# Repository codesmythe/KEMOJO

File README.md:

# KEMOJO (Keyboard / Mouse / Joystick)

This board provides PS/2 keyboard, PS/2 mouse and Atari or MSX (single
button only) joystick support for an RCBus system. It uses the 40-pin
RCBus interface. 

The keyboard, mouse and joystick inputs are read by an ATmega 328P
microcontoller. (This is the same MCU that is in the Arduino UNO.) The
ATmega implements the [Atari ST IKBD
protcol](https://archive.org/details/Intelligent_Keyboard_ikbd_Protocol_Feb_26_1985/)
and communicates that protocol serially to an RCBus system via a
16C550 UART.

## Table of Contents
* [Hardware Documentation](#hardware-documentation)
  * [Schematic](#schematic)
  * [Connectors](#connectors)
  * [Jumpers](#jumpers)
  * [Bill of Materials](#bill-of-materials)
* [Firmware Documentation](#firmware-documentation)
* [Acknowledgements](#acknowledgements)

## Hardware Documentation

### Schematic

The board was created using [Kicad](https://www.kicad.org) version 8.0.

Click the image to download a PDF version of the schematic.

### Connectors

| Reference | Description                                                  |
| --------- | ------------------------------------------------------------ |
| J1        | In-system Programming (ISP) port for programming the ATmega328P firmware. |
| J2        | Atari or MSX Joystick 0, Male DE9 D-Sub. See J7 jumper settings below. |
| J3        | Atari or MSX Joystick 1, Male DE9 D-Sub. See J8 jumper settings below. |
| J4        | PS/2 6-pin Mini DIN connector for PS/2 keyboard.             |
| J5        | PS/2 6-pin Mini DIN connector for PS/2 mouse.                |
| J6        | [FTDI Friend](https://www.adafruit.com/product/284) connection to 16C550 UART. For debug purposes or UART-only operation. |

### Jumpers

| Reference | Description                             | Comment                                                      |
| --------- | --------------------------------------- | ------------------------------------------------------------ |
| J7, J8    | Atari or MSX operation for Joystick 1/0 | The J7 and J8 jumper blocks configue Joystick 1 and Joystick 0, respectively, for either Atari or MSX joystick operation. In MSX mode, only one fire button is supported. To configure a jumper block for Atari mode, close the top and bottom jumpers, and leave the middle two open. For MSX mode, close the middle two jumpers and leave the top and bottom jumpers open. |
| J9        | I/O Address decode                      | The J9 jumper block controls where in the Z80 I/O space the KEMOJO board will appear. The TL16C550 UART that communicates with the ATmega328 requires eight I/O addresses, and can be configured to appear at I/O addresses 0x08-0x0F, 0x28-0x2F, 0x48-0x4F, 0x68-0x6F, 0x88-0x8F, 0xA8-0xAF, 0xC8-0xCF or 0xE8-0xEF. |
| J10       | Interrupt connection to RCBus           | The board can generate a single interrupt from the TL16C550 UART. Jumper the top two pins of J10 to use the /INT RCBus signal (pin 22) or the bottom two pins to use the RCBus USER1/INT1 signal (pin 37). |
| JP4       | IEx bypass                              | When the JP4 jumper is closed, the RCBus-Z80 IEI signal (pin 37) is connected directly to the IEO signal (pin 38). When closed, the board is disconnected from RCBus pins 37 and 38. The KEMOJO board does not use IEI or IEO. This jumper is provided to propagate the IEI/IEO daisy chained if required by the system. |

### Bill of Materials

[Text file parts list](hardware/KEMOJO_mouser.txt) for pasting into the [Mouser BOM tool](https://www.mouser.com/Bom/CopyPaste) (login required).

Check out the [interactive BOM](https://htmlpreview.github.io/?https://raw.githubusercontent.com/codesmythe/KEMOJO/refs/heads/main/hardware/bom/ibom_V1B.html)
for the board.

To obtain a KEMOJO PCB, download these [Gerbers](https://raw.githubusercontent.com/codesmythe/KEMOJO/refs/heads/main/hardware/KEMOJO_V1B.zip) for use at your preferred PCB manufacturer. I use JLCPCB. 

| Component Type     | Reference      | Qty | Description                                | Part                                                                                     |
| ------------------ | -------------- | --- | ------------------------------------------ | ---------------------------------------------------------------------------------------- |
| Capacitor          | C1,C2,C3,C4,C5 |   5 | 0.1 uF, MLCC, 5 mm Pitch                   | Mouser [594-K104K15X7RF5WH5](https://www.mouser.com/ProductDetail/594-K104K15X7RF5WH5)   |
| Diode              | D1             |   1 | 3 mm, yellow LED indicator                 | Mouser [859-LTL-4251N](https://www.mouser.com/ProductDetail/859-LTL-4251N)               |
| Connnector         | J1             |   1 | 2x3 straight pin header                    | Mouser [200-TSW10307TD](https://www.mouser.com/ProductDetail/200-TSW10307TD)             |
| Connector          | J2,J3          |   2 | D-Sub DE9 Male, right angle, PCB mount     | Mouser [523-L7SDE9PA4CH4RC39](https://www.mouser.com/ProductDetail/523-L7SDE9PA4CH4RC39) |
| Connector          | J4,J5          |   2 | Circular 6-pin Mini Din Connector for PS/2 | Mouser [490-MD-40SM](https://www.mouser.com/ProductDetail/490-MD-40SM)                   |
| Connector          | J6             |   1 | 1x6 right angle pin header                 | Mouser [737-PH1RB-06-UA](https://www.mouser.com/ProductDetail/737-PH1RB-06-UA)           |
| Jumper Block       | J7,J8          |   2 | 2x4 straight pin header                    | Mouser [200-TSW10407TD](https://www.mouser.com/ProductDetail/200-TSW10407TD)             |
| Jumper Block       | J9             |   1 | 2x8 straight pin header                    | Mouser [200-TSW10807TD](https://www.mouser.com/ProductDetail/200-TSW10807TD)             |
| Jumper Block       | J10            |   1 | 2x2 straight pin header                    | Mouser [200-TSW10207TD](https://www.mouser.com/ProductDetail/200-TSW10207TD)             |
| Connector          | J11            |   1 | 1x40 right angle pin header                | Mouser [710-61304011021](https://www.mouser.com/ProductDetail/710-61304011021)           |
| Jumper Block       | J12            |   1 | 2x2 straight pin header                    | Mouser [200-TSW10207TD](https://www.mouser.com/ProductDetail/200-TSW10207TD)             |
| Jumper             | JP4            |   1 | 1x2 straight pin header                    | Mouser [200-TSW10207TS](https://www.mouser.com/ProductDetail/200-TSW10207TS)             |
| Transistor         | Q1             |   1 | 2N7000  MOSFET in TO92                     | Mouser [512-2N7000](https://www.mouser.com/ProductDetail/512-2N7000)                     |
| Resistor           | R11            |   1 | 470 ohm, axial, 1% tolerance, 1/4 W        | Mouser [603-MFR-25FTF52-470R](https://www.mouser.com/ProductDetail/603-MFR-25FTF52-470R) |
| Integrated Circuit | U1             |   1 | ATmega328P MCU in 28-pin DIP               | Mouser [556-ATMEGA328P-PU](https://www.mouser.com/ProductDetail/556-ATMEGA328P-PU)       |
| Integrated Circuit | U2             |   1 | TL16C550 UART in 44-pin PLCC               | Mouser [595-TL16C550CFNR](https://www.mouser.com/ProductDetail/595-TL16C550CFNR)         |
| Integrated Circuit | U3             |   1 | 74LS138 in 16-pin DIP                      | Mouser [595-SN74LS138NE4](https://www.mouser.com/ProductDetail/595-SN74LS138NE4)         |
| Integrated Circuit | U4             |   1 | 74LS04 in 14-pin DIP                       | Mouser [595-SN74LS04NE4](https://www.mouser.com/ProductDetail/595-SN74LS04NE4)           |
| Oscillator         | X1             |   1 | 7.3278 MHz can oscillator in 8-pin DIP     | Mouser [774-MXO45HS-3C-7.3](https://www.mouser.com/ProductDetail/774-MXO45HS-3C-7.3)     |
| Socket             | Socket for U1  |   1 | 28-pin DIP socket                          | Mouser [737-ICS-328-T](https://www.mouser.com/ProductDetail/737-ICS-328-T)               |
| Socket             | Socket for U2  |   1 | 44-pin PLCC socket                         | Mouser [575-944424](https://www.mouser.com/ProductDetail/575-944424)                     |
| Socket             | Socket for U3  |   1 | 16-pin DIP socket                          | Mouser [571-1-2199298-4](https://www.mouser.com/ProductDetail/571-1-2199298-4)           |
| Socket             | Socket for U4  |   1 | 14-pin DIP socket                          | Mouser [571-1-2199298-3](https://www.mouser.com/ProductDetail/571-1-2199298-3)           |
| Socket             | Socket for X1  |   1 | 8-pin oscillator socket                    | Mouser [535-1108800](https://www.mouser.com/ProductDetail/535-1108800)                   |

## Acknowledgements

This project has initially inspired by the [Atari ST Eiffel 3](http://didier.mequignon.free.fr/eiffel-e.htm)
project. I've replaced the PIC microcontroller in that project with
an easier-to-use ATmega 328P.

The low-level PS/2 code watches the PS/2 keyboard and mouse clock
lines for transitions and signals an interrupt the ATmega. This code
then reads in PS/2 bytes and buffers them. It was written by Daniel
Cliche (@danodus) and is made available by him under an MIT license
from [here](https://github.com/danodus/rosco_m68k_io).

The higher level code that implements the Atari ST IKDB protocol is
borrowed from the [Hatari](https://www.hatari-emu.org) Atari ST
emulator. It is made available under the GNU GPL, version 2 or higher. 

The overall project thus uses the GNU GPL, version 2 or higher.

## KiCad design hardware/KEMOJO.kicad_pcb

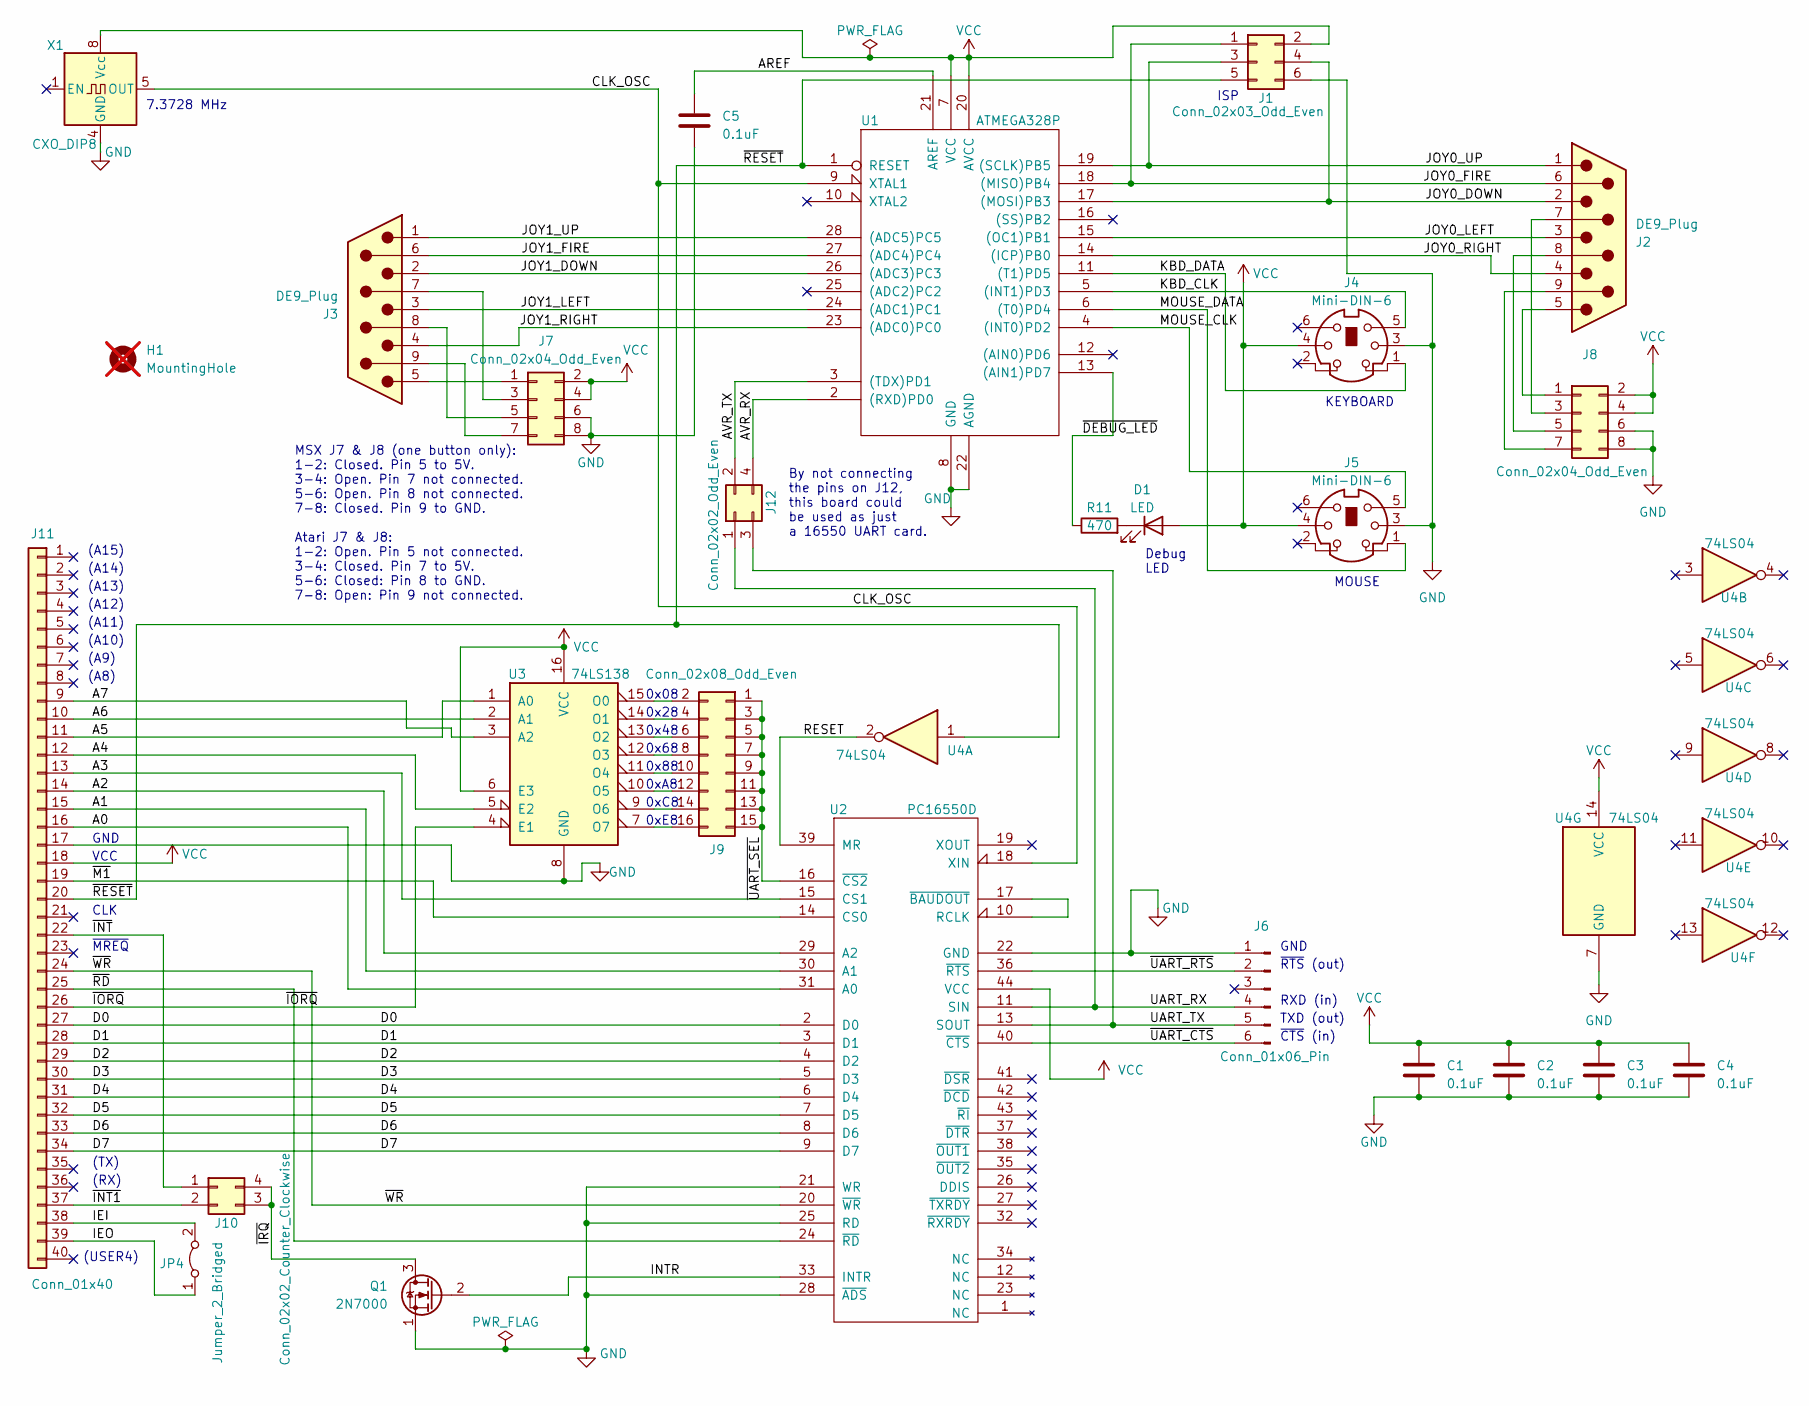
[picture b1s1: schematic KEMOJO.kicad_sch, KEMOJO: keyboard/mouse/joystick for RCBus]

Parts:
C1, C2, C3, C4, C5: 0.1uF; C_Rect_L7.0mm_W2.0mm_P5.00mm; PartNum00 594-K104K15X7RF5WH5
D1: LED; LED_D3.0mm; PartNum00 859-LTL-4251N
H1: MountingHole; MountingHole_3.2mm_M3; not fitted
J1: Conn_02x03_Odd_Even; PinHeader_2x03_P2.54mm_Vertical; PartNum00 200-TSW10307TD
J2, J3: DE9_Plug; DSUB-9_Male_Horizontal_P2.77x2.84mm_EdgePinOffset4.94mm_Hou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; PartNum00 523-L7SDE9PA4CH4RC39
J4, J5: Mini-DIN-6; mini_din; PartNum00 490-MD-40SM
J6: Conn_01x06_Pin; PinHeader_1x06_P2.54mm_Vertical; PartNum00 737-PH1RB-06-UA
J7, J8: Conn_02x04_Odd_Even; PinHeader_2x04_P2.54mm_Vertical; PartNum00 200-TSW10407TD
J9: Conn_02x08_Odd_Even; PinHeader_2x08_P2.54mm_Vertical; PartNum00 200-TSW10807TD
J10: Conn_02x02_Counter_Clockwise; PinHeader_2x02_P2.54mm_Vertical; PartNum00 200-TSW10207TD
J11: Conn_01x40; PinHeader_1x40_P2.54mm_Vertical; PartNum00 710-61304011021
J12: Conn_02x02_Odd_Even; PinHeader_2x02_P2.54mm_Vertical; PartNum00 200-TSW10207TD
JP4: Jumper_2_Bridged; PinHeader_1x02_P2.54mm_Vertical; PartNum00 200-TSW10207TS
Q1: 2N7000; TO-92_HandSolder; PartNum00 512-2N7000
R11: 470; R_Axial_DIN0207_L6.3mm_D2.5mm_P7.62mm_Horizontal; PartNum00 603-MFR-25FTF52-470R
U1: ATMEGA328P; DIP-28_W7.62mm_Socket_LongPads; PartNum00 556-ATMEGA328P-PU
U2: PC16550D; PLCC-44_THT-Socket; PartNum00 595-TL16C550CFNR
U3: 74LS138; DIP-16_W7.62mm_Socket_LongPads; PartNum00 595-SN74LS138NE4
U4: 74LS04; DIP-14_W7.62mm_Socket_LongPads; PartNum00 595-SN74LS04NE4
X1: CXO_DIP8; Oscillator_DIP-8; PartNum00 774-MXO45HS-3C-7.3

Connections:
/A0: J11.16, U2.31 (A0)
/A1: J11.15, U2.30 (A1)
/A2: J11.14, U2.29 (A2)
/A3: J11.13, U2.15 (CS1)
/A4: J11.12, U3.5 (E2)
/A5: J11.11, U3.1 (A0)
/A6: J11.10, U3.2 (A1)
/A7: J11.9, U3.3 (A2)
/AREF: C5.2, U1.21 (AREF)
/AVR_RX: J12.4, U1.2 ((RXD)PD0)
/AVR_TX: J12.2, U1.3 ((TDX)PD1)
/CLK_OSC: U1.9 (XTAL1), U2.18 (XIN), X1.5 (OUT)
/D0: J11.27, U2.2 (D0)
/D1: J11.28, U2.3 (D1)
/D2: J11.29, U2.4 (D2)
/D3: J11.30, U2.5 (D3)
/D4: J11.31, U2.6 (D4)
/D5: J11.32, U2.7 (D5)
/D6: J11.33, U2.8 (D6)
/D7: J11.34, U2.9 (D7)
/IEI: J11.38, JP4.2 (B)
/IEO: J11.39, JP4.1 (A)
/INTR: Q1.2 (G), U2.33 (INTR)
/JOY0_DOWN: J1.4, J2.2, U1.17 ((MOSI)PB3)
/JOY0_FIRE: J1.1, J2.6, U1.18 ((MISO)PB4)
/JOY0_LEFT: J2.3, U1.15 ((OC1)PB1)
/JOY0_RIGHT: J2.4, U1.14 ((ICP)PB0)
/JOY0_UP: J1.3, J2.1, U1.19 ((SCLK)PB5)
/JOY1_DOWN: J3.2, U1.26 ((ADC3)PC3)
/JOY1_FIRE: J3.6, U1.27 ((ADC4)PC4)
/JOY1_LEFT: J3.3, U1.24 ((ADC1)PC1)
/JOY1_RIGHT: J3.4, U1.23 ((ADC0)PC0)
/JOY1_UP: J3.1, U1.28 ((ADC5)PC5)
/KBD_CLK: J4.5, U1.5 ((INT1)PD3)
/KBD_DATA: J4.1, U1.11 ((T1)PD5)
/MOUSE_CLK: J5.5, U1.4 ((INT0)PD2)
/MOUSE_DATA: J5.1, U1.6 ((T0)PD4)
/RESET: U2.39 (MR), U4.2
/UART_RX: J6.4, J12.1, U2.11 (SIN)
/UART_TX: J6.5, J12.3, U2.13 (SOUT)
/~DEBUG_LED: R11.1, U1.13 ((AIN1)PD7)
/~INT1: J10.2, J11.37
/~INT: J10.1, J11.22
/~IORQ: J11.26, U3.4 (E1)
/~IRQ: J10.3, J10.4, Q1.3 (D)
/~M1: J11.19, U2.14 (CS0)
/~RD: J11.25, U2.24 (~RD)
/~RESET: J1.5, J11.20, U1.1 (RESET), U4.1
/~UART_CTS: J6.6, U2.40 (~CTS)
/~UART_RTS: J6.2, U2.36 (~RTS)
/~UART_SEL: J9.1, J9.3, J9.5, J9.7, J9.9, J9.11, J9.13, J9.15, U2.16 (~CS2)
/~WR: J11.24, U2.20 (~WR)
GND: C1.1, C2.1, C3.1, C4.1, C5.1, J1.6, J4.3, J5.3, J6.1, J7.6, J7.8, J8.6, J8.8, J11.17, Q1.1 (S), U1.8 (GND), U1.22 (AGND), U2.21 (WR), U2.22 (GND), U2.25 (RD), U2.28 (~ADS), U3.8 (GND), U4.7 (GND), X1.4 (GND)
unnamed: D1.1 (K), R11.2
unnamed: J3.5, J7.1
unnamed: J3.7, J7.3
unnamed: J3.8, J7.5
unnamed: J3.9, J7.7
unnamed: J2.5, J8.1
unnamed: J2.7, J8.3
unnamed: J2.8, J8.5
unnamed: J2.9, J8.7
unnamed: J9.2, U3.15 (O0)
unnamed: J9.4, U3.14 (O1)
unnamed: J9.6, U3.13 (O2)
unnamed: J9.8, U3.12 (O3)
unnamed: J9.10, U3.11 (O4)
unnamed: J9.12, U3.10 (O5)
unnamed: J9.14, U3.9 (O6)
unnamed: J9.16, U3.7 (O7)
unnamed: U2.10 (RCLK), U2.17 (~BAUDOUT)
VCC: C1.2, C2.2, C3.2, C4.2, D1.2 (A), J1.2, J4.4, J5.4, J7.2, J7.4, J8.2, J8.4, J11.18, U1.7 (VCC), U1.20 (AVCC), U2.44 (VCC), U3.6 (E3), U3.16 (VCC), U4.14 (VCC), X1.8 (Vcc)

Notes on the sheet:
0x48
ISP
RXD (in)
(RX)
By not connecting the pins on J12, this board could be used as just a 16550 UART card.
(A11)
0x68
GND
KEYBOARD
0x28
(A8)
MSX J7 & J8 (one button only): 1-2: Closed. Pin 5 to 5V. 3-4: Open. Pin 7 not connected. 5-6: Open. Pin 8 not connected. 7-8: Closed. Pin 9 to GND. Atari J7 & J8: 1-2: Open. Pin 5 not connected. 3-4: Closed. Pin 7 to 5V. 5-6: Closed: Pin 8 to GND. 7-8: Open: Pin 9 not connected.
~{CTS} (in)
(TX)
0x08
(USER4)
(A15)
~{MREQ}
~{RTS} (out)
0xC8
7.3728 MHz
CLK
TXD (out)
(A12)
0x88
(A14)
(A9)
0xA8
VCC
(A13)
0xE8
(A10)
Debug LED
MOUSE

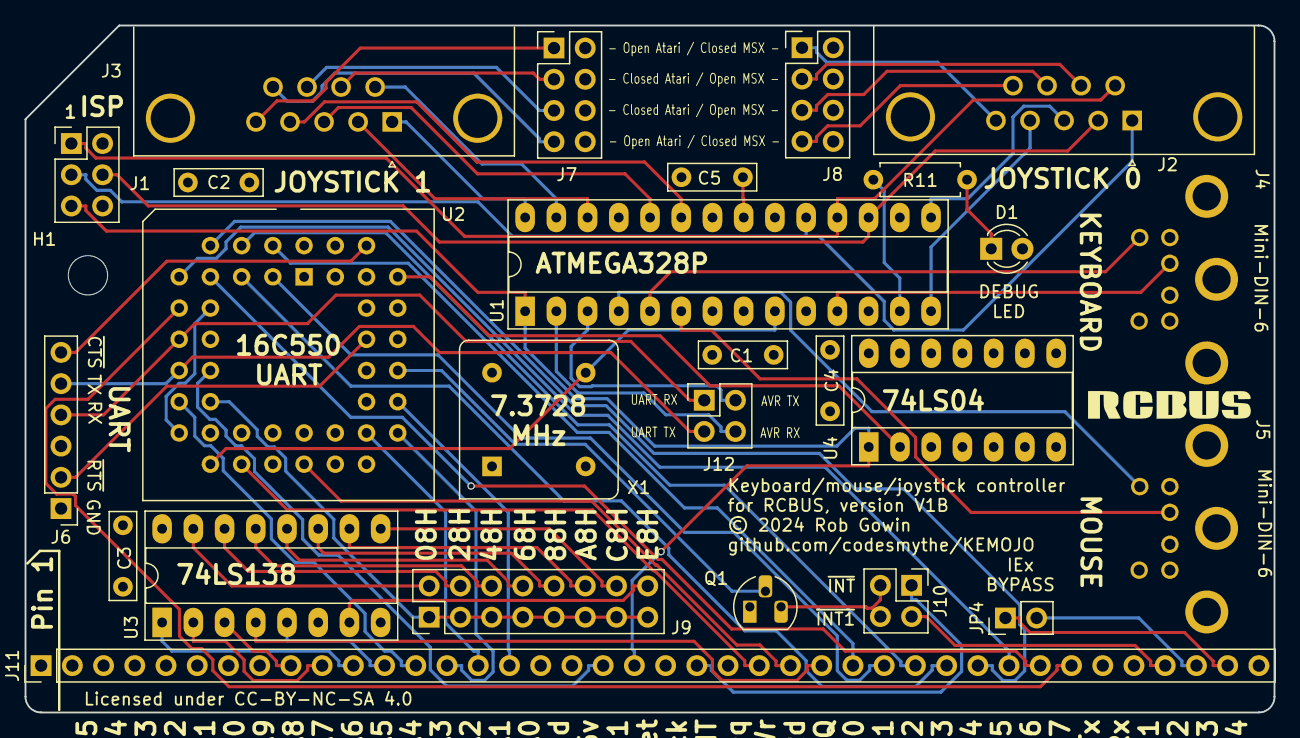
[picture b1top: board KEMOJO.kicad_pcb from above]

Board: 4 copper layers, 101.6 x 55.9 mm, 27 parts (0 on the bottom side), 72 nets.

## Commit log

2025-06-05 Initial commit.
2025-06-05 Comment out caps lock code; update build action.
2025-06-14 Add more documentation.
2025-06-15 Add Gerbers and interactive BOM.
2025-06-15 Fix links in README.md
2025-06-15 Minor tweaks to README.md
2025-06-15 Fix Mouser BOM tool link.
2025-06-15 Tweak BOM listing.

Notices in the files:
hardware/KEMOJO.kicad_pcb:
Licensed under CC-BY-NC-SA 4.0
© 2024 Rob Gowin
hardware/KEMOJO.kicad_sch:
This PCB design © 2024 Rob Gowin.
